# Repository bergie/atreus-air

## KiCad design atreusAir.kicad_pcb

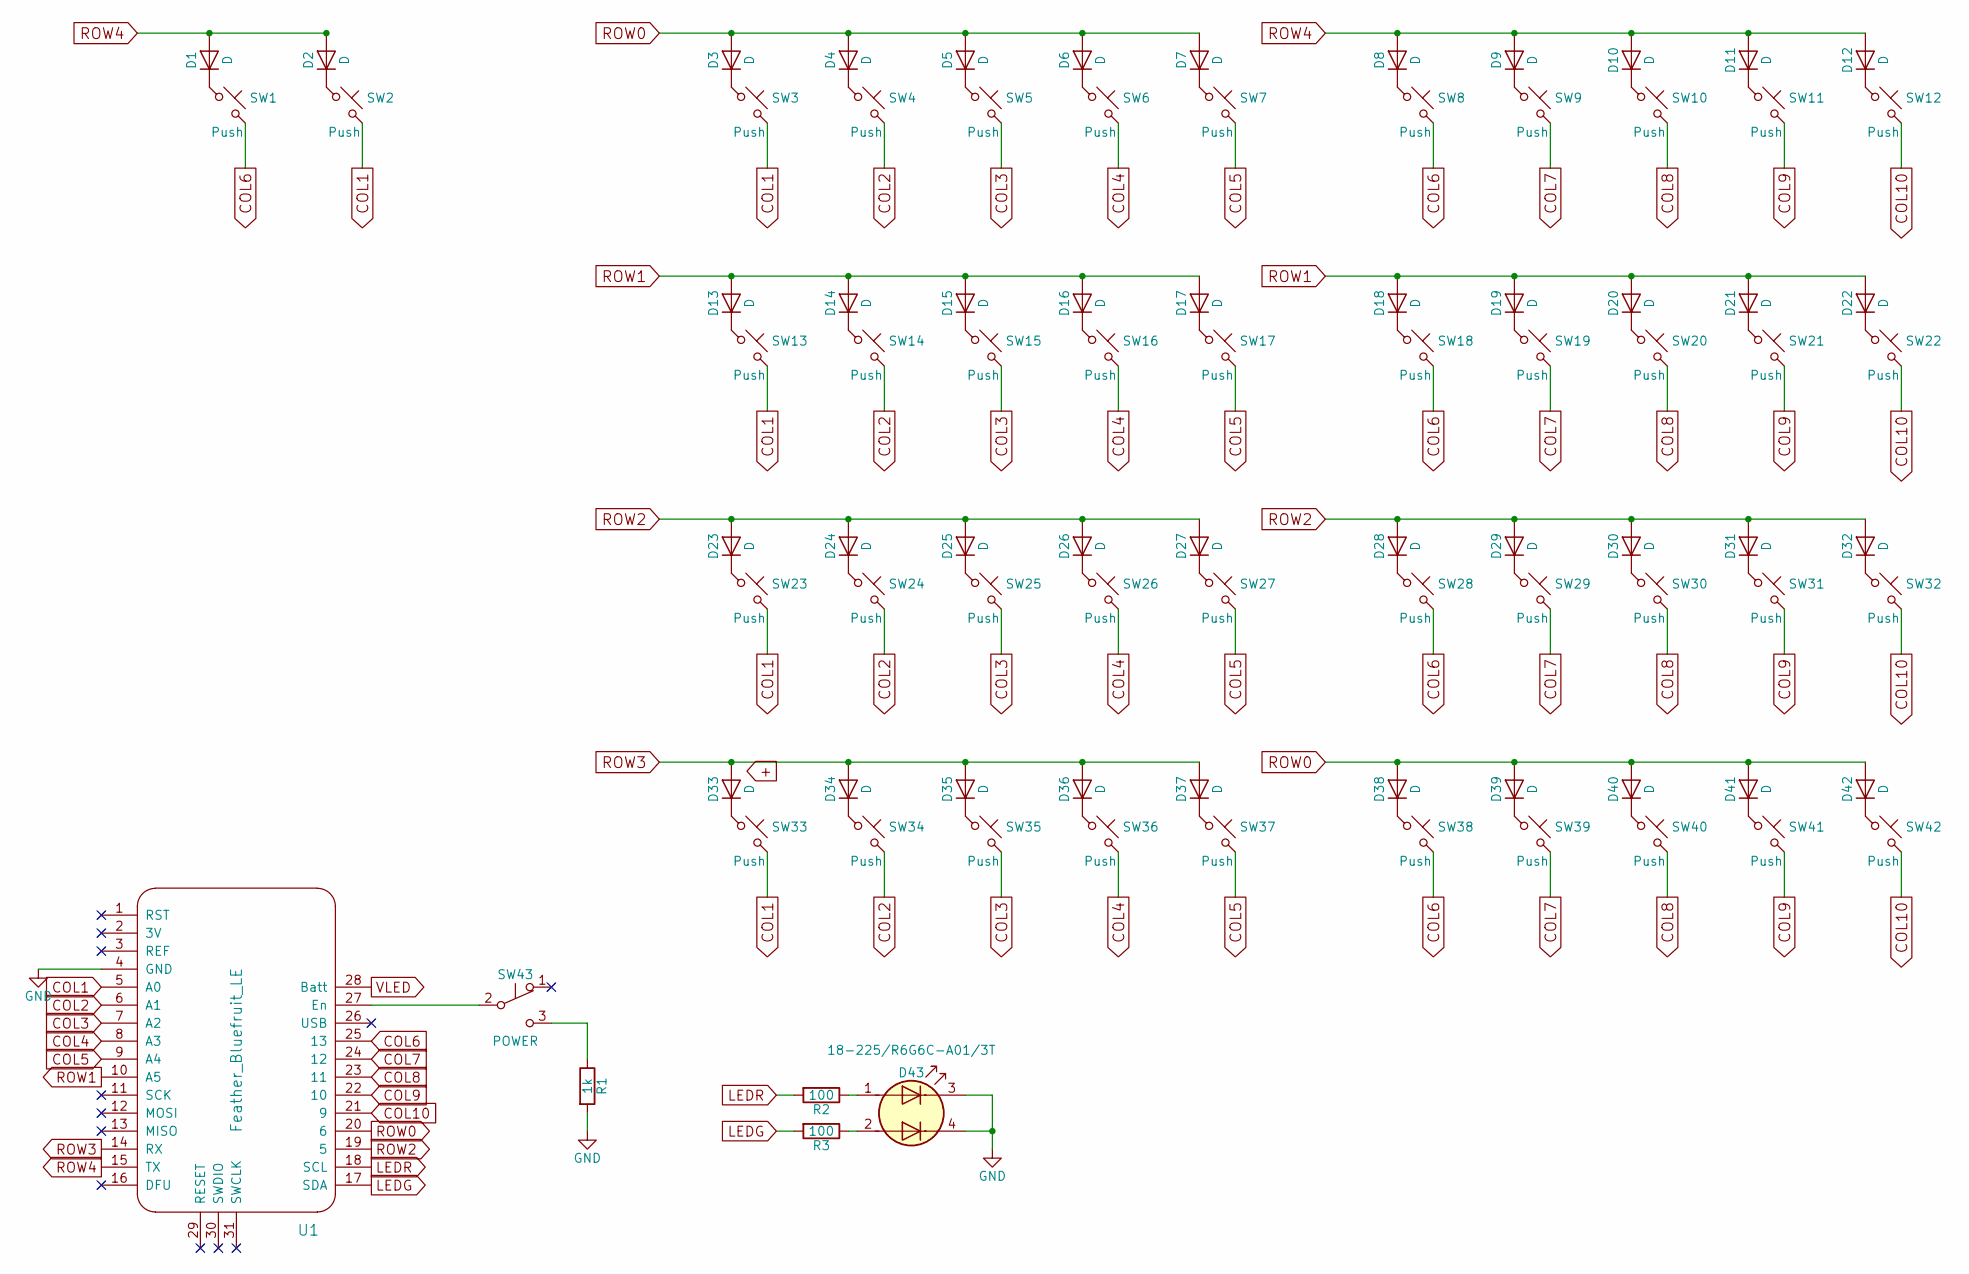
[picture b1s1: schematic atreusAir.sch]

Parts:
D1, D2, D3, D4, D5, D6, D7, D8, D9, D10, D11, D12, D13, D14, D15, D16, D17, D18, D19, D20, D21, D22, D23, D24, D25, D26, D27, D28, D29, D30, D31, D32, D33, D34, D35, D36, D37, D38, D39, D40, D41, D42: D; D_0603
D43: 18-225/R6G6C-A01/3T; R6G6C-A01
R1: 1k; R_0603
R2, R3: 100; R_0603
SW1, SW2, SW3, SW4, SW5, SW6, SW7, SW8, SW9, SW10, SW11, SW12, SW13, SW14, SW15, SW16, SW17, SW18, SW19, SW20, SW21, SW22, SW23, SW24, SW25, SW26, SW27, SW28, SW29, SW30, SW31, SW32, SW33, SW34, SW35, SW36, SW37, SW38, SW39, SW40, SW41, SW42: Push; ASwitch
SW43: POWER; SW_SPDT_PCM12
U1: Feather_Bluefruit_LE; Feather_Bluefruit

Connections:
COL1: SW2.2, SW3.2, SW13.2, SW23.2, SW33.2, U1.5 (A0)
COL2: SW4.2, SW14.2, SW24.2, SW34.2, U1.6 (A1)
COL3: SW5.2, SW15.2, SW25.2, SW35.2, U1.7 (A2)
COL4: SW6.2, SW16.2, SW26.2, SW36.2, U1.8 (A3)
COL5: SW7.2, SW17.2, SW27.2, SW37.2, U1.9 (A4)
COL6: SW1.2, SW8.2, SW18.2, SW28.2, SW38.2, U1.25 (13)
COL7: SW9.2, SW19.2, SW29.2, SW39.2, U1.24 (12)
COL8: SW10.2, SW20.2, SW30.2, SW40.2, U1.23 (11)
COL9: SW11.2, SW21.2, SW31.2, SW41.2, U1.22 (10)
COL10: SW12.2, SW22.2, SW32.2, SW42.2, U1.21 (9)
GND: D43.3 (K1), D43.4 (K2), R1.2, U1.4 (GND)
LEDG: R3.2, U1.17 (SDA)
LEDR: R2.2, U1.18 (SCL)
unnamed: D1.1 (K), SW1.1
unnamed: D2.1 (K), SW2.1
unnamed: D3.1 (K), SW3.1
unnamed: D4.1 (K), SW4.1
unnamed: D5.1 (K), SW5.1
unnamed: D6.1 (K), SW6.1
unnamed: D7.1 (K), SW7.1
unnamed: D8.1 (K), SW8.1
unnamed: D9.1 (K), SW9.1
unnamed: D10.1 (K), SW10.1
unnamed: D11.1 (K), SW11.1
unnamed: D12.1 (K), SW12.1
unnamed: D13.1 (K), SW13.1
unnamed: D14.1 (K), SW14.1
unnamed: D15.1 (K), SW15.1
unnamed: D16.1 (K), SW16.1
unnamed: D17.1 (K), SW17.1
unnamed: D18.1 (K), SW18.1
unnamed: D19.1 (K), SW19.1
unnamed: D20.1 (K), SW20.1
unnamed: D21.1 (K), SW21.1
unnamed: D22.1 (K), SW22.1
unnamed: D23.1 (K), SW23.1
unnamed: D24.1 (K), SW24.1
unnamed: D25.1 (K), SW25.1
unnamed: D26.1 (K), SW26.1
unnamed: D27.1 (K), SW27.1
unnamed: D28.1 (K), SW28.1
unnamed: D29.1 (K), SW29.1
unnamed: D30.1 (K), SW30.1
unnamed: D31.1 (K), SW31.1
unnamed: D32.1 (K), SW32.1
unnamed: D33.1 (K), SW33.1
unnamed: D34.1 (K), SW34.1
unnamed: D35.1 (K), SW35.1
unnamed: D36.1 (K), SW36.1
unnamed: D37.1 (K), SW37.1
unnamed: D38.1 (K), SW38.1
unnamed: D39.1 (K), SW39.1
unnamed: D40.1 (K), SW40.1
unnamed: D41.1 (K), SW41.1
unnamed: D42.1 (K), SW42.1
unnamed: D43.1 (A1), R2.1
unnamed: D43.2 (A2), R3.1
unnamed: R1.1, SW43.3 (C)
unnamed: SW43.2 (B), U1.27 (En)
ROW0: D3.2 (A), D4.2 (A), D5.2 (A), D6.2 (A), D7.2 (A), D38.2 (A), D39.2 (A), D40.2 (A), D41.2 (A), D42.2 (A), U1.20 (6)
ROW1: D13.2 (A), D14.2 (A), D15.2 (A), D16.2 (A), D17.2 (A), D18.2 (A), D19.2 (A), D20.2 (A), D21.2 (A), D22.2 (A), U1.10 (A5)
ROW2: D23.2 (A), D24.2 (A), D25.2 (A), D26.2 (A), D27.2 (A), D28.2 (A), D29.2 (A), D30.2 (A), D31.2 (A), D32.2 (A), U1.19 (5)
ROW3: D33.2 (A), D34.2 (A), D35.2 (A), D36.2 (A), D37.2 (A), U1.14 (RX)
ROW4: D1.2 (A), D2.2 (A), D8.2 (A), D9.2 (A), D10.2 (A), D11.2 (A), D12.2 (A), U1.15 (TX)
VLED: U1.28 (Batt)

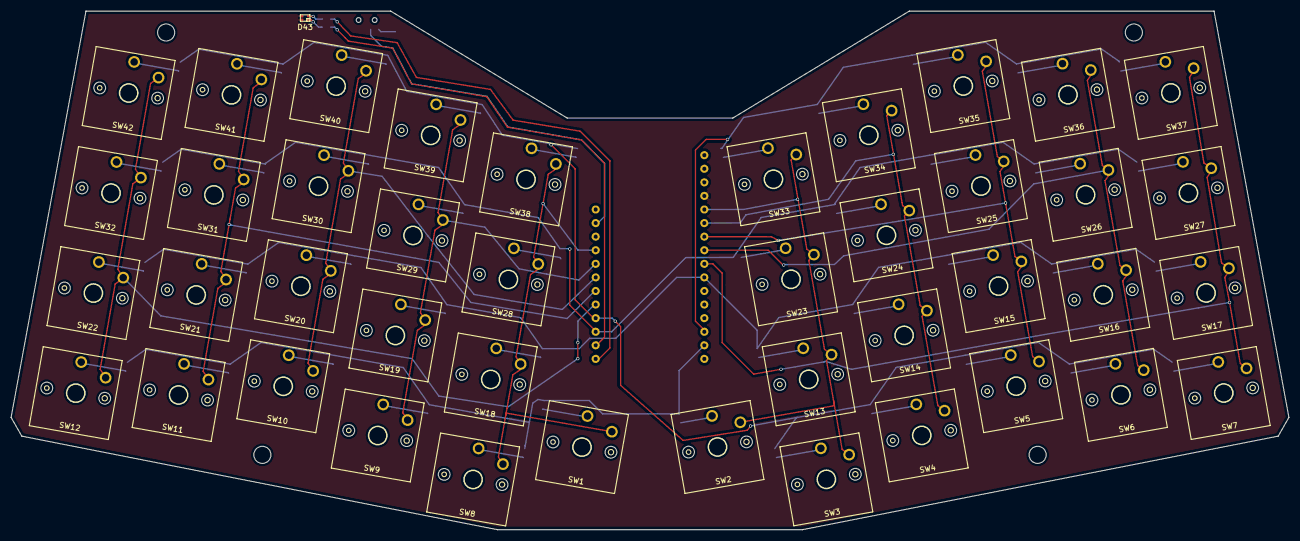
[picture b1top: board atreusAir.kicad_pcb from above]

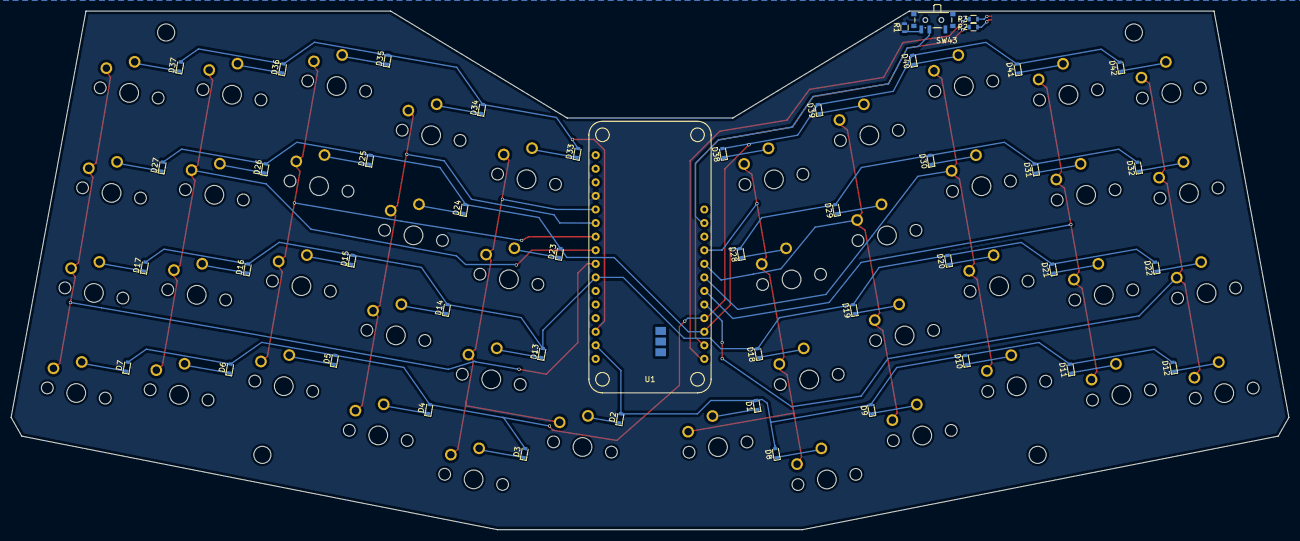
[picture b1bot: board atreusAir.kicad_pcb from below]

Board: 2 copper layers, 239.0 x 97.0 mm, 90 parts (47 on the bottom side), 64 nets.

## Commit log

2019-03-17 funktionierend aber zu dick
2019-03-17 switches sorted but not yet connected
2019-03-17 ausrichtung feather korrigiert ! !
2019-03-20 feather jetzt auf unterseite, leiterbahnen verlegt.
2019-03-23 done. added correct WRL and OBJ files for 3d model
2019-03-29 cleanup
